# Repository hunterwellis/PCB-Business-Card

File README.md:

# PCB Business Card
STM32-based PCB that runs a FFT on an audio input from a MEMS mark displaying the spectrogram on an LED matrix ($4\times8$).

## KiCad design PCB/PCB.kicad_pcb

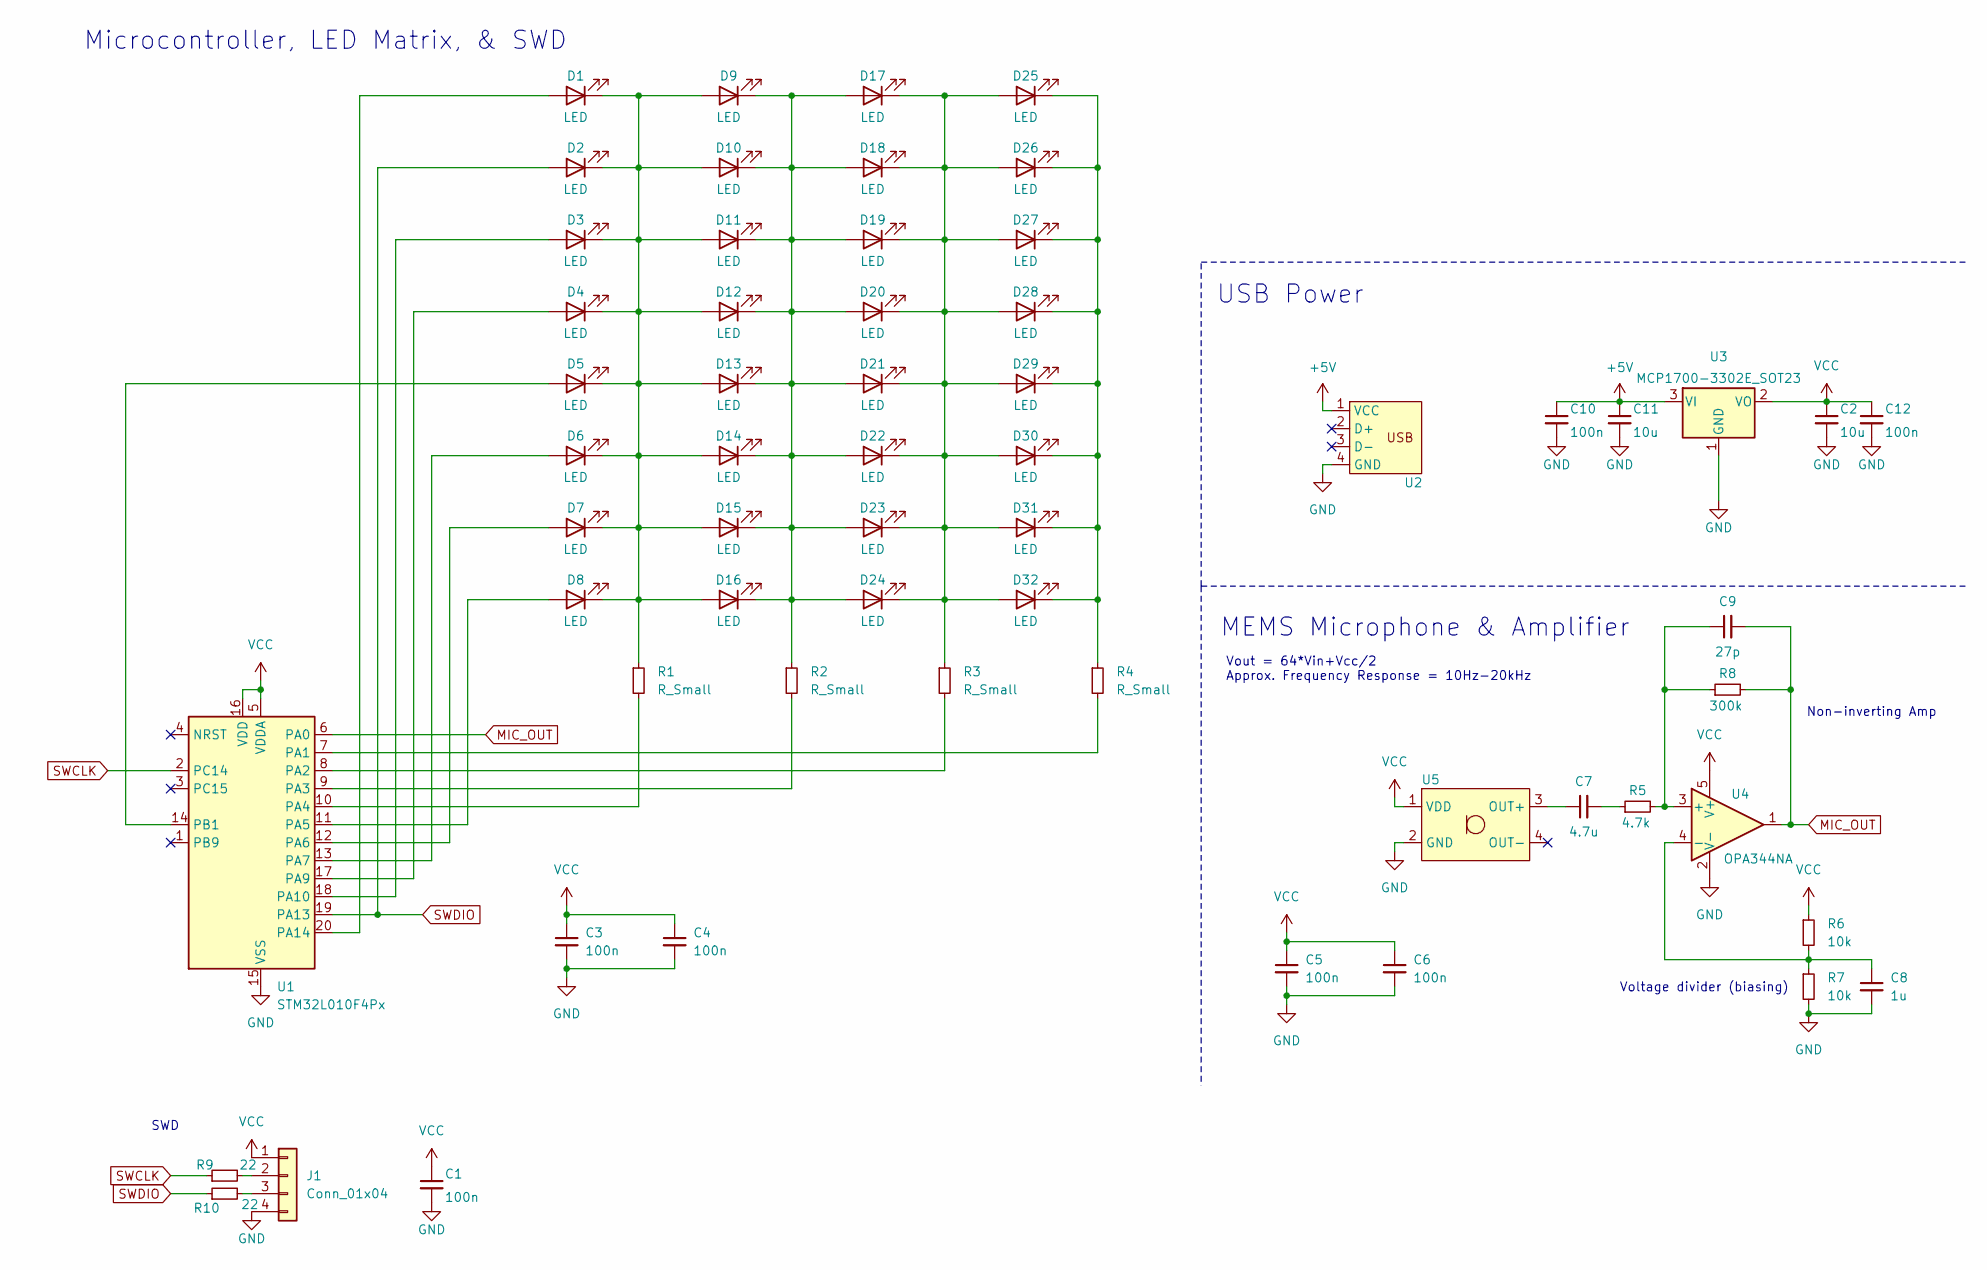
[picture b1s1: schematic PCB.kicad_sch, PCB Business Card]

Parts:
C1, C3, C4, C5, C6, C10, C12: 100n; C_0805_2012Metric
C2, C11: 10u; C_0805_2012Metric
C7: 4.7u; C_0805_2012Metric
C8: 1u; C_0805_2012Metric
C9: 27p; C_0805_2012Metric
D1, D2, D3, D4, D5, D6, D7, D8, D9, D10, D11, D12, D13, D14, D15, D16, D17, D18, D19, D20, D21, D22, D23, D24, D25, D26, D27, D28, D29, D30, D31, D32: LED; LED_0805_2012Metric
J1: Conn_01x04; PinHeader_1x04_P2.54mm_Vertical
R1, R2, R3, R4: R_Small; R_0805_2012Metric
R5: 4.7k; R_0805_2012Metric
R6, R7: 10k; R_0805_2012Metric
R8: 300k; R_0805_2012Metric
R9, R10: 22; R_0805_2012Metric
U1: STM32L010F4Px; TSSOP-20_4.4x6.5mm_P0.65mm
U2: PCB_USB
U3: MCP1700-3302E_SOT23; SOT-23
U4: OPA344NA; SOT-23-5
U5: SPH8878LR5H-1

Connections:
+5V: C10.1, C11.1, U2.1 (VCC), U3.3 (VI)
GND: C1.2, C2.2, C3.2, C4.2, C5.2, C6.2, C8.2, C10.2, C11.2, C12.2, J1.4, R7.2, U1.15 (VSS), U2.4 (GND), U3.1 (GND), U4.2 (V-), U5.2 (GND)
MIC_OUT: C9.2, R8.2, U1.6 (PA0), U4.1
unnamed: C7.2, R5.1
unnamed: D1.2 (A), U1.20 (PA14)
unnamed: D1.1 (K), D2.1 (K), D3.1 (K), D4.1 (K), D5.1 (K), D6.1 (K), D7.1 (K), D8.1 (K), D9.2 (A), D10.2 (A), D11.2 (A), D12.2 (A), D13.2 (A), D14.2 (A), D15.2 (A), D16.2 (A), R1.1
unnamed: D3.2 (A), U1.18 (PA10)
unnamed: D4.2 (A), U1.17 (PA9)
unnamed: D5.2 (A), U1.14 (PB1)
unnamed: D6.2 (A), U1.13 (PA7)
unnamed: D7.2 (A), U1.12 (PA6)
unnamed: D8.2 (A), U1.11 (PA5)
unnamed: D9.1 (K), D10.1 (K), D11.1 (K), D12.1 (K), D13.1 (K), D14.1 (K), D15.1 (K), D16.1 (K), D17.2 (A), D18.2 (A), D19.2 (A), D20.2 (A), D21.2 (A), D22.2 (A), D23.2 (A), D24.2 (A), R2.1
unnamed: D17.1 (K), D18.1 (K), D19.1 (K), D20.1 (K), D21.1 (K), D22.1 (K), D23.1 (K), D24.1 (K), D25.2 (A), D26.2 (A), D27.2 (A), D28.2 (A), D29.2 (A), D30.2 (A), D31.2 (A), D32.2 (A), R3.1
unnamed: D25.1 (K), D26.1 (K), D27.1 (K), D28.1 (K), D29.1 (K), D30.1 (K), D31.1 (K), D32.1 (K), R4.1
unnamed: J1.2, R9.2
unnamed: J1.3, R10.2
unnamed: R4.2, U1.7 (PA1)
unnamed: R3.2, U1.8 (PA2)
unnamed: R2.2, U1.9 (PA3)
unnamed: R1.2, U1.10 (PA4)
unnamed: C9.1, R5.2, R8.1, U4.3 (+)
unnamed: C8.1, R6.2, R7.1, U4.4 (-)
unnamed: C7.1, U5.3 (OUT+)
SWCLK: R9.1, U1.2 (PC14)
SWDIO: D2.2 (A), R10.1, U1.19 (PA13)
VCC: C1.1, C2.1, C3.1, C4.1, C5.1, C6.1, C12.1, J1.1, R6.1, U1.5 (VDDA), U1.16 (VDD), U3.2 (VO), U4.5 (V+), U5.1 (VDD)

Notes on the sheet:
Voltage divider (biasing)
Vout = 64*Vin+Vcc/2 Approx. Frequency Response = 10Hz-20kHz
Non-inverting Amp
SWD
Microcontroller, LED Matrix, & SWD
USB Power
MEMS Microphone & Amplifier

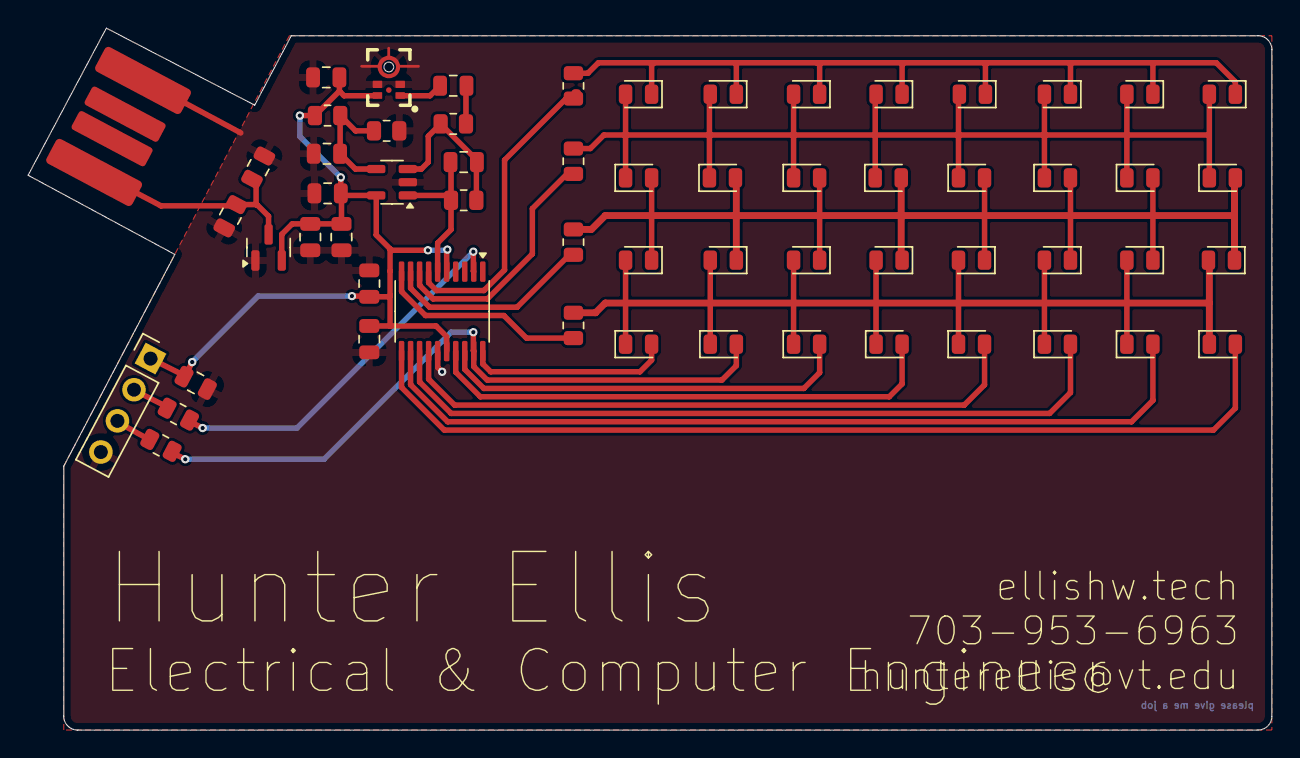
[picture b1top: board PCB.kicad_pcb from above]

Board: 2 copper layers, 89.6 x 50.5 mm, 60 parts (0 on the bottom side), 27 nets.

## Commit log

2024-12-14 init commit
2025-03-16 MEMS microphone, SWD, and PCB trace USB power
